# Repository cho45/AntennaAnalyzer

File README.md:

# AntennaAnalyzer

cho45's AntennaAnalyzer project

# Spec

 * Frequency range: 〜70MHz
 * Measures: SWR, R + j |X|

# Hardware

 * AD9851 DDS
 * Resistive bridge + AD8302 detector
 * LPC1114 (with mbed framework)
 * Bluetooth

# Android App Screen Shots

<img src="https://lh3.googleusercontent.com/JDww9a9jy38Xa3buTkERHQHDOyeMCbTLvD_xkDUBuqNI0r0SvAImQ8pzi2Y1ZVi0UDuLu2_8WA3h4da7imNwu8IF8W7ARn4ZTxPKx7cQda3Lh3onPVps-j_MJ1V86Z-9URh7m4WjvUpNJeGgSzTEqYQXReR0n74YVBcS4JjZuDz5sIT6c6wS7NUifCfXDVNnJHYsLd2-p4lHaMpG6K4dDyCjC03mAzIQ_6BfLT9T13sPf5FsI-FcOGz7dWN1chF0jgvYfAmEjnF3tLocUUWrJN-RqX3CbcD9KrnceK7BTGoHw_E2zaVSuXugG6j17nJTBtmaG_J03aOSjwPx8eu3VSLziUlDj6UBovbsuQEBFZAkxTyKCyNpzSQcQxa9U_9Rn7Tfrkni9NbUTILG8Qi0iOWXtNxskgMo3Et2iJrTBIVb8-jpXvlb1QrRvMFQtSUjqsfY4mm9_NBZzP-XTxeqJmDh55oO7kiQ701XgSNFnUmYcXAJcPvqb9vA_j_sus8KawdXGDwFER42Lsicm8L44HNkx3mijBks28kG0w4UAeA1UwHvAtxOUhJuQPQMzTCrqSC_VQ=w1657-h932-no"/>

<img src="https://lh3.googleusercontent.com/cn8IIEa3besMo8Egxdnaxc7HrYdFsRvc41XRng0XnM_e6o79p79G5Wp3c2d-JFb6O2CM2XZ_k9j9Wqlt-5M8QpTsxvF44BnlI7NXCyy9vGpSIbqYW_Orh5sxJtmilioTYt63fNcnlSS9f4FfcFdXVi10he2zM12z35iJF3ZRUSwawwsHYsG8PcCaByVgeHS6bCIEIuXCgnRkA5TmVUSIFSbihUSEiulSI5sqlfPOV0LRUmlC_8jCNEzye1v6rDwHCv8iN7gLG3DTDl45sZKZSRJZIw5mAY60axCdO9C5AktEJkLVDZ3SVbh9jAfdAjKQ5QempF39RH83s87DzqA7OrJxgPle6IrZSCiGpyd5raizFFf7ugu5cH7E-ZWLE5T7VaHVCJLy0AMt9tb9G_7Yt5C2R2VSiMFXh6witNdJhxTcixL9KReRwVZ-EQrfewYQLuxIPqZPx-oMAHWIOro1ZFk03eBTMa5fRDQiv719kR4BdG5W79g4hOLz8i1pXXP2lMor0hAsE0xwB33ii4v9xP1yHvwHdHukd_7XnoVW1iiyCXMgRaS6yB1Ee3tYQ5ZR7DVEXw=w1657-h932-no"/>

<img src="https://lh3.googleusercontent.com/1KaaPIo95jZxo4gb9HQH3JP7SrcWNsz2uzYxZ5_BW-Gf4WfPJWPJ4-JO3i5I-OnOuLh6pVZlFYHTTADqZQ08GsdnGyBE4S1Pi5ku_IbmhPesPiFaI2v5n9U-Gvw7bm_25Vz3B61YFtK7I7-_OQLe-SLKHLmch6_JQ2u356fSPzRBvPNFCRUMlhb-D4YDlMtsqvCHyF611m0Gd9wa249Eyt1uo7E1wi4gVCPAj19qQHQzJVwr8eIPeNIi4ysXEARoUmcsLzZwBIs0jAYXD081juiw7aw9-vslq3XPl2MG9439jzFbdCIou-B0eoJg0j5Zs_zeWG9VH0-5XuFU8sXkb9Bpf2tL4c-ibg7OJpMgPHoZg0tfbMSfHF_rrrG-i-igEqUMCWqtc7wLIGM6EsbY30fCxKlZ7jOu4SntxzcKT9xu2ieSXUna3gVlgjMqlj4TRffRmemFBxefUpaRfryQtp7zg5kQnPowzR3qq14L3_rxZ63hua7gR1FLLaDPk_Aua_Wk-M_jOr5nTi7il8TkgGxxnCh6epwgteiHvJrE98REd7vp120at_et2-ztq369-Wh6gA=w1657-h932-no"/>

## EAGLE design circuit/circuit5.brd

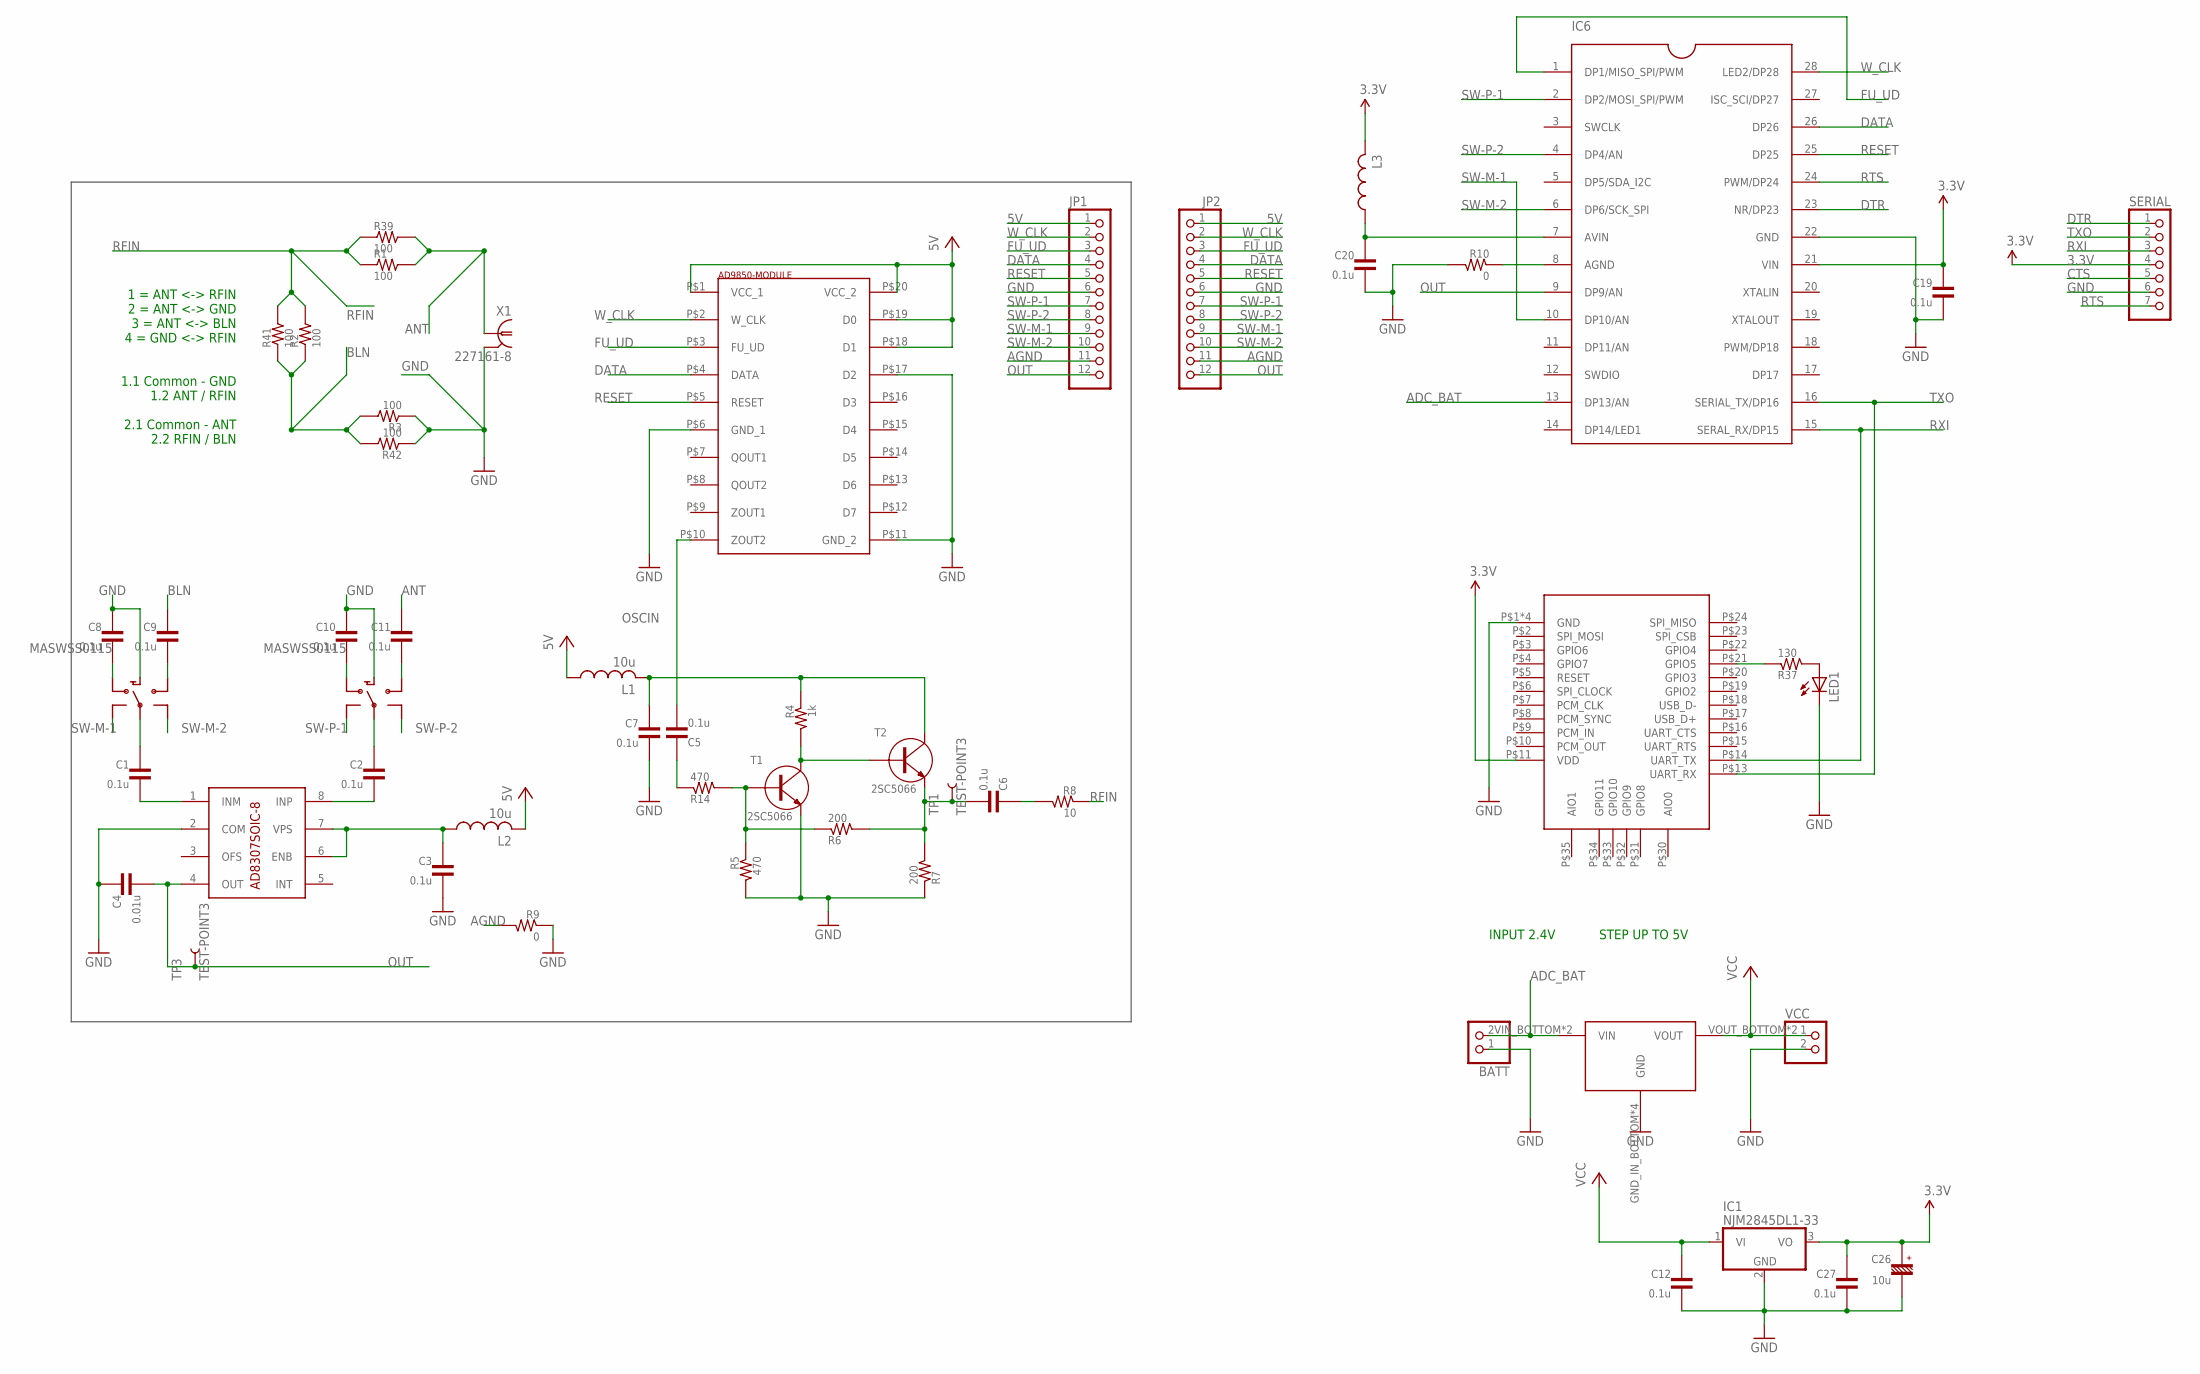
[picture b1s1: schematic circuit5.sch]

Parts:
BATT: PINHD-1X2; 1X02
C1, C2, C3, C5, C6, C7, C8, C9, C10, C11, C12, C19, C20, C27: 0.1u; CP1608
C4: 0.01u; CP1608
C26: 10u; 16V-4-2.54
IC1: NJM2845DL1-33; TO252
IC6: LPC1114FN28; DIP28
JP1, JP2: PINHD-1X12; 1X12
L1, L2: 10u; CP1608
L3: L-; CP1608
LED1: LED3MM
R1, R2, R3, R39, R41, R42: 100; CP1608
R4: 1k; CP1608
R5, R14: 470; CP1608
R6, R7: 200; CP1608
R8: 10; CP1608
R9, R10: 0; CP1608
R37: 130; CP1608
SERIAL: PINHD-1X7; 1X07
T1, T2: 2SC5066; SSM
TP1, TP3: TEST-POINT3; PAD.03X.03
U$1: AD9850-MODULE
U$2: RN-42
U$3: AD8307SOIC-8; SO08
U$4: DC-DCSX1308; DC-DC-SX1308
U$5, U$6: MASWSS0115; SOT363
VCC: PINHD-1X2; 1X02
X1: 227161-8; AMP_227161

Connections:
3.3V: C19.SMD1 (1), C26.+, C27.SMD1 (1), IC1.3 (VO), IC6.21 (VIN), L3.SMD2 (2), SERIAL.4, U$2.P$11 (VDD)
5V: C12.SMD1 (1), IC1.1 (VI), JP1.1, JP2.1, L1.SMD1 (1), L2.SMD2 (2), U$1.P$1 (VCC_1), U$1.P$18 (D1), U$1.P$19 (D0), U$1.P$20 (VCC_2), U$4.VOUT_BOTTOM (VOUT), U$4.VOUT_TOP (VOUT), VCC.1
+12V-ANALOG: C7.SMD1 (1), L1.SMD2 (2), R4.SMD1 (1), T2.P$3 (C)
ADC_BAT: BATT.2, IC6.13 (DP13/AN), U$4.VIN_BOTTOM (VIN), U$4.VIN_TOP (VIN)
AGND: IC6.8 (AGND), JP1.11, JP2.11, R9.SMD2 (2), R10.SMD1 (1)
ANT: C11.SMD1 (1), R1.SMD2 (2), R39.SMD2 (2), X1.1
BLN: C9.SMD1 (1), R2.SMD1 (1), R3.SMD2 (2), R41.SMD1 (1), R42.SMD2 (2)
CTS: SERIAL.5
DATA: IC6.26 (DP26), JP1.4, JP2.4, U$1.P$4 (DATA)
DTR: IC6.23 (NR/DP23), SERIAL.1
FU_UD: IC6.1 (DP1/MISO_SPI/PWM), JP1.3, JP2.3, U$1.P$3 (FU_UD)
GND: BATT.1, C3.SMD2 (2), C4.SMD1 (1), C7.SMD2 (2), C8.SMD1 (1), C10.SMD1 (1), C12.SMD2 (2), C19.SMD2 (2), C20.SMD2 (2), C26.-, C27.SMD2 (2), IC1.2 (GND), IC6.22 (GND), JP1.6, JP2.6, LED1.K (C), R3.SMD1 (1), R5.SMD2 (2), R7.SMD1 (1), R9.SMD1 (1), R10.SMD2 (2), R42.SMD1 (1), SERIAL.6, T1.P$2 (E), U$1.P$6 (GND_1), U$1.P$11 (GND_2), U$1.P$17 (D2), U$2.P$1 (GND), U$2.P$12 (GND), U$2.P$28 (GND), U$2.P$29 (GND), U$3.2 (COM), U$4.GND_IN_BOTTOM (GND), U$4.GND_IN_TOP (GND), U$4.GND_OUT_BOTTOM (GND), U$4.GND_OUT_TOP (GND), U$5.2 (GND), U$6.2 (GND), VCC.2, X1.2
unnamed: C2.SMD1 (1), U$6.5 (COMMON)
unnamed: C1.SMD1 (1), U$5.5 (COMMON)
unnamed: R4.SMD2 (2), T1.P$3 (C), T2.P$1 (B)
unnamed: R5.SMD1 (1), R6.SMD1 (1), R14.SMD2 (2), T1.P$1 (B)
unnamed: C8.SMD2 (2), U$5.3 (RF2)
unnamed: C6.SMD2 (2), R6.SMD2 (2), R7.SMD2 (2), T2.P$2 (E), TP1.P$1
unnamed: C1.SMD2 (2), U$3.1 (INM)
unnamed: C2.SMD2 (2), U$3.8 (INP)
unnamed: C3.SMD1 (1), L2.SMD1 (1), U$3.6 (ENB), U$3.7 (VPS)
unnamed: C9.SMD2 (2), U$5.1 (RF1)
unnamed: C10.SMD2 (2), U$6.3 (RF2)
unnamed: C5.SMD1 (1), R14.SMD1 (1)
unnamed: C11.SMD2 (2), U$6.1 (RF1)
unnamed: C6.SMD1 (1), R8.SMD2 (2)
unnamed: C20.SMD1 (1), IC6.7 (AVIN), L3.SMD1 (1)
unnamed: LED1.A, R37.SMD2 (2)
unnamed: R37.SMD1 (1), U$2.P$21 (GPIO5)
OSCIN: C5.SMD2 (2), U$1.P$10 (ZOUT2)
OUT: C4.SMD2 (2), IC6.9 (DP9/AN), JP1.12, JP2.12, TP3.P$1, U$3.4 (OUT)
RESET: IC6.25 (DP25), JP1.5, JP2.5, U$1.P$5 (RESET)
RFIN: R1.SMD1 (1), R2.SMD2 (2), R8.SMD1 (1), R39.SMD1 (1), R41.SMD2 (2)
RTS: IC6.24 (PWM/DP24), SERIAL.7
RXI: IC6.15 (SERAL_RX/DP15), SERIAL.3, U$2.P$14 (UART_TX)
SW-M-1: IC6.10 (DP10/AN), JP1.9, JP2.9, U$5.4 (V2)
SW-M-2: IC6.6 (DP6/SCK_SPI), JP1.10, JP2.10, U$5.6 (V1)
SW-P-1: IC6.2 (DP2/MOSI_SPI/PWM), JP1.7, JP2.7, U$6.4 (V2)
SW-P-2: IC6.4 (DP4/AN), JP1.8, JP2.8, U$6.6 (V1)
TXO: IC6.16 (SERIAL_TX/DP16), SERIAL.2, U$2.P$13 (UART_RX)
W_CLK: IC6.28 (LED2/DP28), JP1.2, JP2.2, U$1.P$2 (W_CLK)

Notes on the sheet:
1 = ANT <-> RFIN 2 = ANT <-> GND 3 = ANT <-> BLN 4 = GND <-> RFIN 1.1 Common - GND 1.2 ANT / RFIN 2.1 Common - ANT 2.2 RFIN / BLN
INPUT 2.4V
STEP UP TO 5V

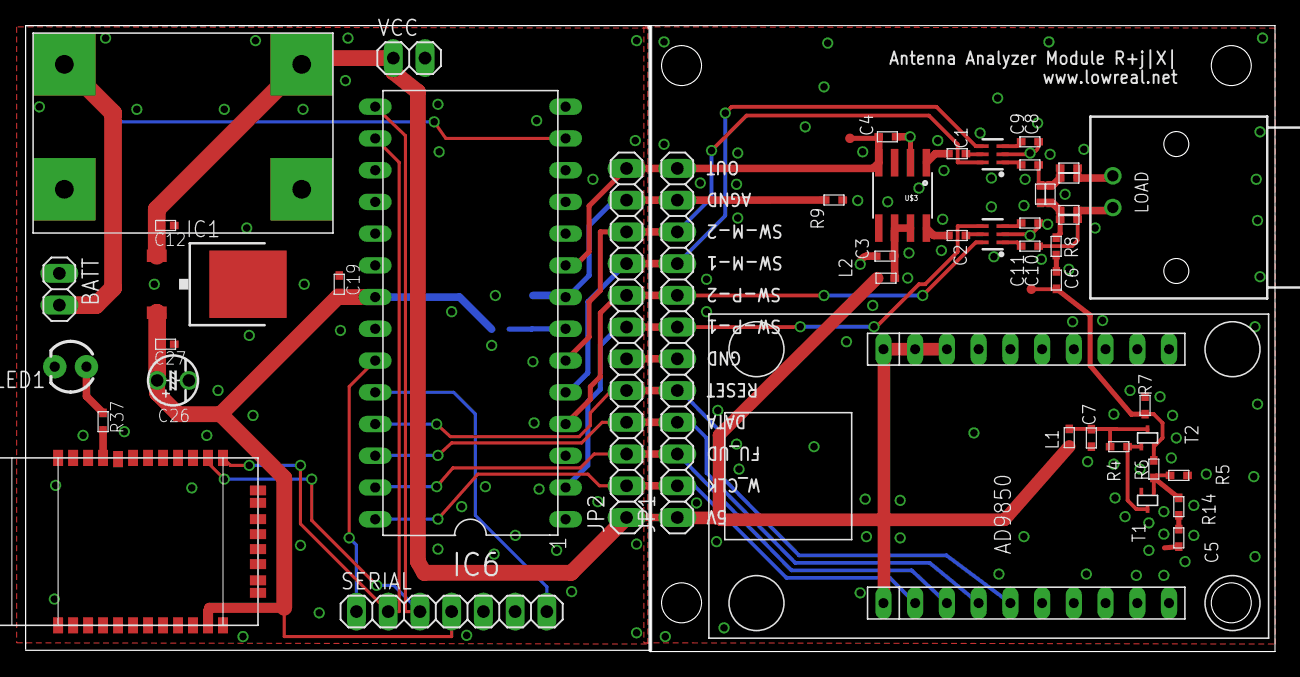
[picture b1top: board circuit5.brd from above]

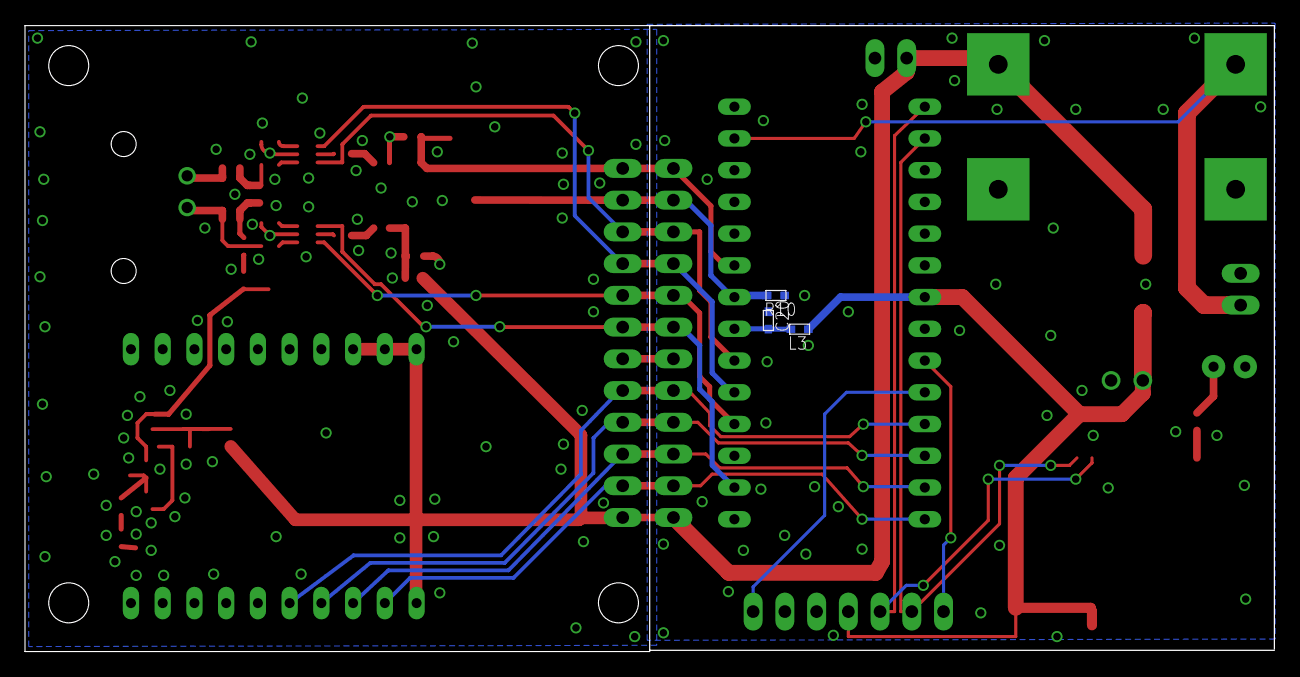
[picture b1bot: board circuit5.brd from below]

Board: 2 copper layers, 100.0 x 50.0 mm, 53 parts (3 on the bottom side), 40 nets.

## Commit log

2016-03-27 init
2016-03-27 append immediate stop feature
2016-03-30 append ruby sample code
2016-03-30 update cordova project
2016-03-30 readme

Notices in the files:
parts and their libraries:
SparkFun-Passives: Licensing: CC v3.0 Share-Alike You are welcome to use this library for commercial purposes.
